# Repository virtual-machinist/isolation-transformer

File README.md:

# Isolation Transformer Project

Control circuitry for a 2600 VA isolation transformer. My first electronics project in KiCad.

## Motivation

As you might have guessed it, the primary reason I did this project was to learn the ropes of modern EDA.

Prior to using KiCad my circuit design consisted of:

1. Designing the actual circuit on paper or in a circuit editor tool similar to [sPlan](http://www.virtualworkbench.com/splan.html).  
2. Simulating the circuit if possible. A long time ago I used Electronics Workbench (EWB), but I had trouble running it on my system recently, so now I use the (in-)famous [Circuit Simulator Applet](https://www.falstad.com/circuit/).  
3. Buying some parts to build a prototype on a breadboard. The prototype not only served to verify the circuit works, but also helped to think through how to lay the parts out on the PCB.  
4. Designing a PCB either in [Sprint-Layout](http://www.virtualworkbench.com/sprint-layout.html) or on paper and scan it afterwards.  
5. Printing the layout on a transfer film and etching masked PCB in ferric chloride.  
6. Cutting PCBs to size, drilling holes, tinning traces, etc.  
7. Halfway through assembly realizing that a couple of pins got accidentally swapped. Sometimes it was possible to fix the problem using an x-acto + couple of bodge wires. Sometimes it was back to step 4.

Having spare time only on weekends the whole project could take a couple of months to finish, which wasn't great.

The build quality was _okay_ for any finished project, but you couldn't do more complex stuff like vias and multi-layered PCBs.

In 2019 we have FOSS and cloud-based EDA tools with impressive component libraries, PCBs for $2 in less than a week, so the more tedious bits are being taken care of. Now you can:

1. Design the schematic in EDA suite like KiCad.  
2. Simulate the schematic if possible and correct the design.  
In theory KiCad has SPICE integration so this can be done even faster, although I never tried this myself.  
3. Make a breadboard prototype if needed.  
4. Design the PCB in EDA suite. Most commonly used components already have a footprint in the library, but it's not hard making your own.  
5. Export Gerber files to PCB manufacturer.  
6. Assemble the circuit.

This takes considerably less time than it used to. The EDA helps to avoid dumb mistakes like swapping pins. You can do complex multi-layered designs. The PCB manufacturers make your project look professional.

## Purpose

You would want to use an isolation transformer if you:

* Repair mains stuff.
* Design mains stuff.
* Use vintage stuff on tubes without proper galvanic isolation.

## Disclaimer

_**Without going any further please read and understand the following:**_  

**This project deals with voltages that may potentially injure or even kill you. Should you attempt to make something similar you are doing this at your own risk!**

## Basic Theory

An isolation transformer galvanically isolates the load from mains providing the same voltage. In theory nothing is needed besides the transformer itself and a suitable enclosure with an outlet.

However above a certain power rating transformers have a very high inrush current and will trip the mains breaker if plugged in as-is.

A soft-start circuit is needed that limits the current to a safe level initially, but later allows operation with maximum current.

The simplest soft-start circuit consists of a negative temperature coefficient (NTC) resistor connected in series with the load. An NTC has a somewhat high resistance when cold and a very low resistance when hot. NTCs are typically used in switch-mode power supplies (SMPS) to limit the current drawn by charging filter capacitors. Once turned on the NTC maintains its high temperature through ohmic heating.

However an NTC doesn't cool down instantaneously after being turned off and thus cannot limit current if the load is turned on instantaneously. This isn't a big issue for SMPS, as capacitors do not instantaneously discharge either, but can be a problem for inductive loads.

This is why a more complex circuit has to be used for transformers that "emulates" the behavior of an NTC - a resistor in parallel with a normally opened relay is connected in series with the transformer. After a small delay enough to stabilize the current the relay closes, shorting the resistor. This type of circuit is used for example in microwave ovens.

We would also want the load of the transformer to be disconnected before the soft-start circuit has finished its sequence. This way the load will not try to start operating with sub-mains voltage and limited current.

## Parts Used

Here are some notes about the parts used for this project. Not all parts are listed here, not all parts were bought especially for this project. My goal was to reuse as much as possible surplus parts from previous endeavors.

* Enclosure - SZOMK AK40023. Dimensions: 250x150x300 mm. Was probably the hardest part to get for this project. There's many cheap but smaller boxes available on eBay/AliExpress, but anything that would fit the transformer + give a few cm of space for control circuitry and outlets cost insane money (three-digit figures, not kidding). Luckily bought this one directly from the manufacturer for ~$50 + shipping.

* PCBs were ordered from JLCPCB in a batch of 5 for ~$40 including shipping. Although they charged me extra for 2oz copper and having "two designs" per set of gerbers, the price is still very competitive.

* `TR1` - Main transformer. A custom 2600 VA toroidal transformer ordered especially for this project from a reputable local manufacturer for ~$220. Has four windings - two primary and two secondary. Each winding is done using 125 turns of 3x1.32mm enameled copper wire (thus, primary and secondary sides have 250 turns each).  
Net weight of transformer core alone is ~10kg, net weight of copper used is ~5kg. Transformer total weight is 15.5kg.  
May in theory provide ~3 kVA output power if properly cooled.

* `PS1` - 12V 4W DC SMPS module. Left over from previous projects. Bought for ~$5 from either eBay or AliExpress, don't remember.

* `FL1` - EMI suppression filter for `PS1`. Left over from previous projects. Bought from eBay for under $3. Although `PS1` has _some_ filtering built-in I added this for good measure.

* `R14` - soft-start circuit ballast resistor. 300R 200W is probably an overkill, but I had this lying around from a failed project and couldn't think of any better use. Originally bought from eBay for $16.

* `NE1`..`NE3` - 220V panel-mount neon indicators. Each one has an integrated 150K resistor. Bought a pack of 10 for under $2 from AliExpress.

* `F1`, `F2` - 94°C 16A thermal fuses attached to the sides of `TR1`. Bought as a pack of 10 from AliExpress for under $4. Tested one from the batch on a water bath with a digital thermometer, fails at around 94°C as expected.

* `CB1` - 250V 15A resettable panel-mount circuit breaker. Bought for ~$2 from eBay.

* `K1`..`K4` relays sit on a relay socket, `K5` and `K6` are directly soldered to the PCB.

* `U3` is a 5V buck regulator pin-compatible with LM7805. Used for increased efficiency. Bought as a pack of 10 for ~$15 + shipping from AliExpress.

* `U4` is actually К155ЛА3, a Soviet pin-compatible 7400 replacement.

* `J1`, `J7`, `J10` - generic blue 2-pin terminal block connectors with 5.08mm spacing left over from previous projects.

* `J2`..`J6`, `J8`, `J9` - 300V 30A rated terminal block connector by a Chinese manufacturer CIXI MEIGAN with 9.52mm spacing. Didn't test them at maximum rating, but look quite beefy. Connectors are in fact made of copper. Bought as a pack of 20 for ~$11 from eBay. Were the only ones I could find that would fit a square crimped ferrule with 6mm2 cable.

* `SW1` - 250V 15A DPDT switch with middle off position. Bought for under $2 as a pack of 2 from eBay. Both were tested at near maximum rating, one was discarded for too high voltage drop and unreliable switching.

* `SW2` and `SW3` tested and salvaged from disassembled devices.  
Although `SW3` could be beefier (or control a separate 16A relay) the primary function of this device is galvanic isolation, i.e. floating ground, not mains conditioning. Besides that there is a rather short path to chassis from the outlets, so probably not a problem anyway.

* High-current wiring done with EN 50525-2-31 insulated 6mm2 multi-strand copper wire bought especially for this project. Low-current wiring done with 0.75-1.5mm2 multi-strand copper wire leftovers.  
All wires were crimped untinned with either spade connectors or ferrules to avoid insulation damage due to heat.

## Operation Mode

You can open the [schematic](Images/isolation-transformer.sch.pdf) for better understanding.

1. Normally `SW1` is in middle position and the device is off.

2. When `SW1` is turned in **II** position direct mode is engaged and mains power is routed directly to `TR1`. `PS1` remains unpowered, relays `K1`..`K4` output power to `J12` (230V outlet) through their normally closed contacts. Depending on the input voltage `NE1` may or may not light up.

3. When `SW1` is turned in **I** position soft-start mode is engaged and power is routed through the soft-start circuit to `TR1`. Both relays `K5` and `K6` remain off, effectively leaving `TR1` disconnected from mains. At the same time `PS1` starts powering both soft-start and 115V/230V mode selection circuit.

4. `K2` in mode selection circuit is immediately activated, disconnecting `TR1` from any set of outputs (`J12`..`J14`). Mode selection logic is disabled.

5. At ~500ms from power on `K5` in activated, connecting `TR1` to mains through `R14`.

6. At ~1.1s from power on `K6` shorts `R14`, effectively completing the soft-start sequence.

7. At ~2.4s from power on 115V/230V mode selection logic is re-enabled:  
    * If `SW2` is on, 115V mode is selected. `K1`, `K3` and `K4` are activated in addition to already active `K2`. Outputs `J13` and `J14` become live, `NE2` and `NE3` light up.
    * if `SW2` is off, 230V mode is selected. `K2` is deactivated, output `J12` becomes live, `NE1` lights up.

## Photos

PCBs from JLCPCB:

Back panel close-up during final testing and assembly:

Overall view before closing the enclosure:

Assembled front panel:

Assembled back panel:

## Contributing

If you have any questions or remarks for this design, feel free to open an issue.

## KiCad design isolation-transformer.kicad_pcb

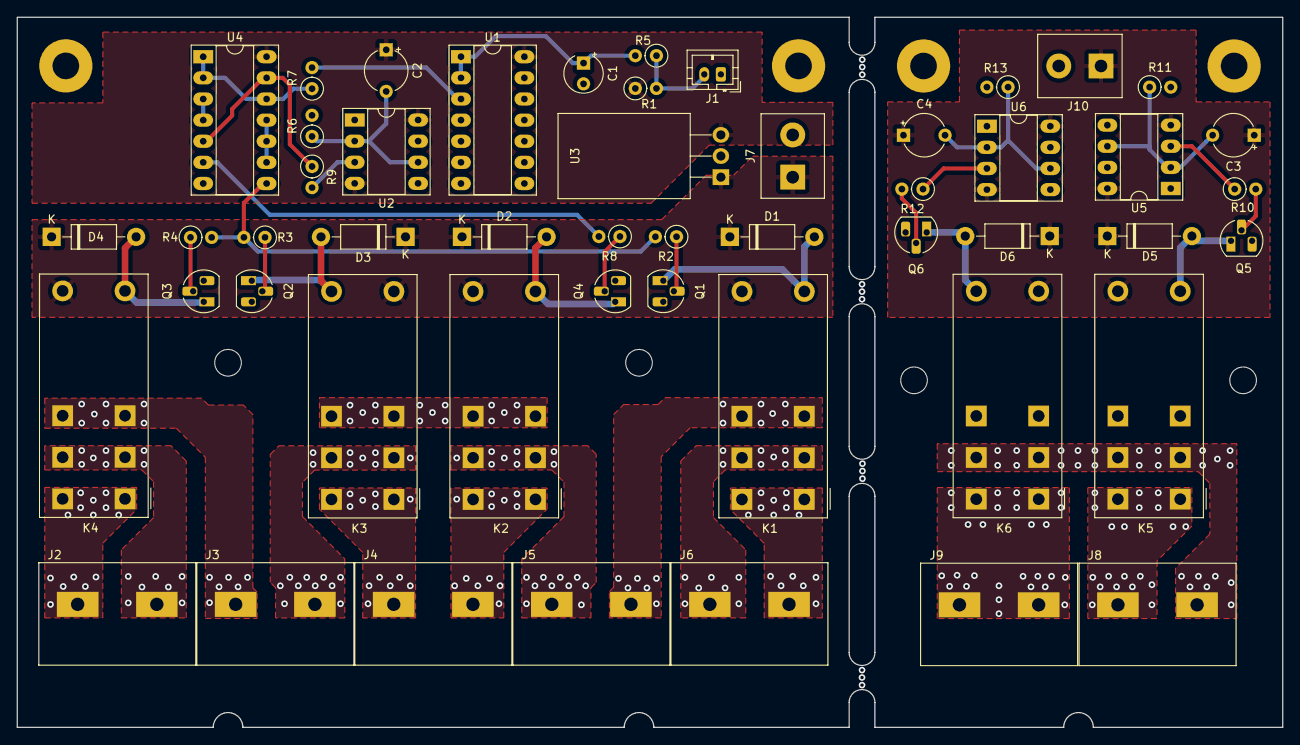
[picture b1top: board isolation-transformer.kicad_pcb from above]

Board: 2 copper layers, 152.1 x 85.4 mm, 59 parts (0 on the bottom side), 44 nets.

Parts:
C1: 1uF; CP_Radial_Tantal_D4.5mm_P2.50mm
C2, C3, C4: 47uF; CP_Radial_Tantal_D5.0mm_P5.00mm
D1, D2, D3, D4, D5, D6: 1N4007; D_DO-41_SOD81_P10.16mm_Horizontal
J1: MODE; JST_PH_B2B-PH-K_1x02_P2.00mm_Vertical
J2, J3, J4, J5, J6, J8, J9: MG950-9.5; TerminalBlock_CixiMeigan_MG950-9.5-2_P9.52mm
J7, J10: PWR; TerminalBlock_bornier-2_P5.08mm_no_line
K1, K2, K3, K4: G2R-1-E-12VDC; Relay_SPDT_Omron_G2R-1-E
K5, K6: FTR-K1CK012W; Relay_SPDT_Fujitsu_FTR-K1C
MT1, MT2, MT5, MT6: M3; MountingHole_3.2mm_M3_Pad
MT3, MT4, MT7, MT8: M3; MountingHole_3.2mm_M3
Q1, Q2, Q3, Q4, Q5, Q6: BC546; TO-92_HandSolder
R1: 82k; R_Axial_DIN0207_L6.3mm_D2.5mm_P2.54mm_Vertical
R2, R3, R4: 3k; R_Axial_DIN0207_L6.3mm_D2.5mm_P2.54mm_Vertical
R5: 18k; R_Axial_DIN0207_L6.3mm_D2.5mm_P2.54mm_Vertical
R6: 47k; R_Axial_DIN0207_L6.3mm_D2.5mm_P2.54mm_Vertical
R7: 10; R_Axial_DIN0207_L6.3mm_D2.5mm_P2.54mm_Vertical
R8, R9: 1k; R_Axial_DIN0207_L6.3mm_D2.5mm_P2.54mm_Vertical
R10, R12: 9k1; R_Axial_DIN0207_L6.3mm_D2.5mm_P2.54mm_Vertical
R11: 10k; R_Axial_DIN0207_L6.3mm_D2.5mm_P2.54mm_Vertical
R13: 22k; R_Axial_DIN0207_L6.3mm_D2.5mm_P2.54mm_Vertical
U1: HEF4093B; DIP-14_W7.62mm_Socket_LongPads
U2, U5, U6: NE555; DIP-8_W7.62mm_Socket_LongPads
U3: DD4012SB_5V; TO-220-3_Horizontal_TabDown_NoHole
U4: 7400; DIP-14_W7.62mm_Socket_LongPads

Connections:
+5V: C2.1, R1.1, U1.14 (VCC), U2.4 (R), U2.8 (VCC), U3.3 (VO), U4.14 (VCC)
+12V: C3.1, C4.1, D1.1 (K), D2.1 (K), D3.1 (K), D4.1 (K), D5.1 (K), D6.1 (K), J7.1, J10.1, K1.8, K2.8, K3.1, K4.8, K5.5, K6.4, U3.1 (VI), U5.4 (R), U5.8 (VCC), U6.4 (R), U6.8 (VCC)
/Mode Selection/115V_1_L: J6.2, K1.4, K1.5
/Mode Selection/115V_1_N: J4.2, K2.4, K2.5
/Mode Selection/115V_2_L: J4.1, K3.4, K3.5
/Mode Selection/115V_2_N: J2.1, K4.4, K4.5
/Mode Selection/230V_L: J5.2, K1.2, K1.7
/Mode Selection/230V_N: J3.1, K4.2, K4.7
/Mode Selection/MODE_SELECT: R7.2, U1.3
/Mode Selection/MODE_SW: J1.2, R1.2, R5.1
/Mode Selection/ON_DELAY: R9.2, U2.3 (Q)
/Mode Selection/RELAY_1_3_4: R2.2, R3.2, R4.2, U4.8
/Mode Selection/RELAY_2: R8.2, U4.6
/Mode Selection/W5: J6.1, K1.3, K1.6
/Mode Selection/W6: J5.1, K2.3, K2.6
/Mode Selection/W7: J3.2, K3.3, K3.6
/Mode Selection/W8: J2.2, K4.3, K4.6
/Soft Start/BALLAST_1: J8.2, K5.2, K5.7, K6.2, K6.7
/Soft Start/BALLAST_2: J9.1, J9.2, K6.1, K6.8
/Soft Start/BALLAST_RELAY: D6.2 (A), K6.5, Q6.1 (C)
/Soft Start/ON_RELAY: D5.2 (A), K5.4, Q5.1 (C)
/Soft Start/PWR_1: J8.1, K5.1, K5.8
GND: C1.2, J1.1, J7.2, J10.2, MT1.1, MT2.1, MT5.1, MT6.1, Q1.3 (E), Q2.3 (E), Q3.3 (E), Q4.3 (E), Q5.3 (E), Q6.3 (E), R6.2, R11.2, R13.2, U1.7 (GND), U2.1 (GND), U3.2 (GND), U4.7 (GND), U5.1 (GND), U6.1 (GND)
unnamed: C1.1, R5.2, U1.1, U1.2
unnamed: C2.2, R6.1, U2.2 (TR), U2.6 (THR)
unnamed: C3.2, R11.1, U5.2 (TR), U5.6 (THR)
unnamed: C4.2, R13.1, U6.2 (TR), U6.6 (THR)
unnamed: D1.2 (A), K1.1, Q1.1 (C)
unnamed: D2.2 (A), K2.1, Q4.1 (C)
unnamed: D3.2 (A), K3.8, Q2.1 (C)
unnamed: D4.2 (A), K4.1, Q3.1 (C)
unnamed: K2.2, K2.7, K3.2, K3.7
unnamed: Q1.2 (B), R2.1
unnamed: Q2.2 (B), R3.1
unnamed: Q3.2 (B), R4.1
unnamed: Q4.2 (B), R8.1
unnamed: Q5.2 (B), R10.2
unnamed: Q6.2 (B), R12.2
unnamed: R7.1, U4.1, U4.2, U4.12
unnamed: R9.1, U4.5, U4.13
unnamed: R10.1, U5.3 (Q)
unnamed: R12.1, U6.3 (Q)
unnamed: U4.3, U4.4
unnamed: U4.9, U4.10, U4.11

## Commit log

2018-12-24 First prototype
2019-01-13 Fixes in mode selection logic
2019-01-13 Fix relay firing order in soft-start
2019-10-03 Final schematic version
2019-10-06 Actually used parts instead of generic ones
2019-10-09 Readme
2019-10-09 Add project license
2019-10-09 Typo, clarification
2019-10-10 Readme corrections, photos
2019-10-10 More corrections, rendered schematic PDF
2019-10-10 Add PCB photos, fixes in schematics, add lost PCB track
2019-10-10 Ignore generated netlist files
2023-02-03 Migrate to KiCad 6
